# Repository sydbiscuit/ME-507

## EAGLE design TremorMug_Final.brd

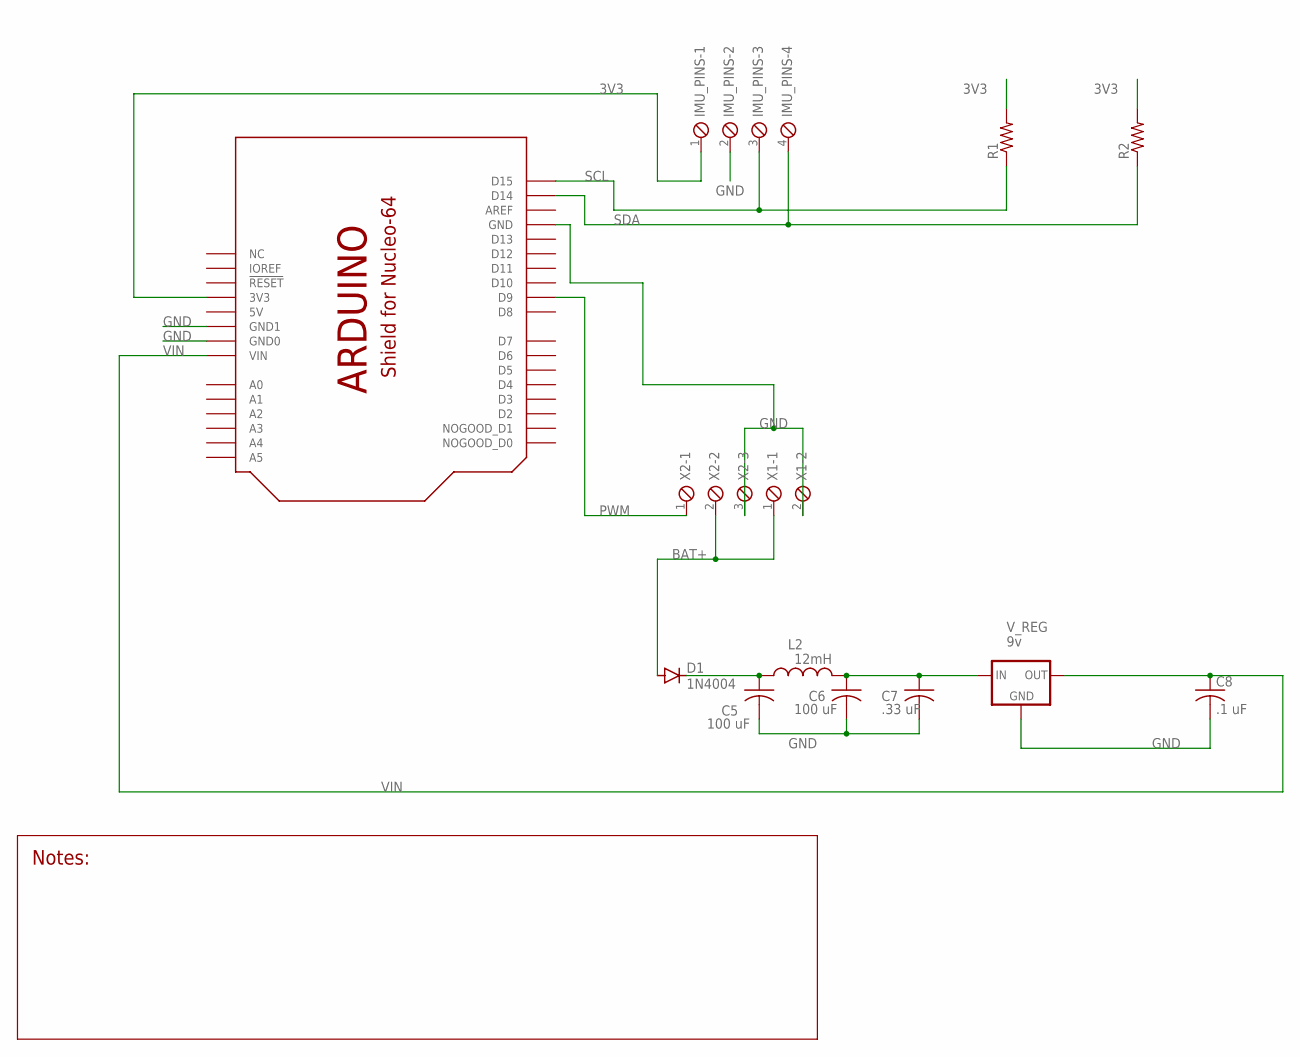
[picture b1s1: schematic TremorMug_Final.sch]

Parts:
C5, C6: 100 uF; C050-045X075
C7: .33 uF; C0805
C8: .1 uF; C0805
D1: 1N4004; DO41-10
IMU_PINS: SCREWTERM_4P_254; 4POL254
L2: 12mH; 0207/5V
R1, R2: R-US_0204/7; 0204/7
U$1: SHIELD_FOR_NUCLE0_64_STANDARD; SHIELD_FOR_NUCLEO_64_STD
V_REG: 9v; 78MXXL
X1: SCREWTERM_2P_508; 2POL508
X2: SCREWTERM_3P_381; 3POL381

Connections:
3V3: IMU_PINS.1, R1.2, R2.2, U$1.3V (3V3)
5V: U$1.5V
BAT+: D1.A, X1.1, X2.2
GND: C5.2, C6.2, C7.2, C8.2, IMU_PINS.2, U$1.GND, U$1.GND1 (GND0), U$1.GND2 (GND1), V_REG.GND, X1.2, X2.3
unnamed: C6.1, C7.1, L2.2, V_REG.IN
unnamed: C5.1, D1.C, L2.1
PWM: U$1.D9, X2.1
SCL: IMU_PINS.3, R1.1, U$1.D15
SDA: IMU_PINS.4, R2.1, U$1.D14
VIN: C8.1, U$1.VIN, V_REG.OUT

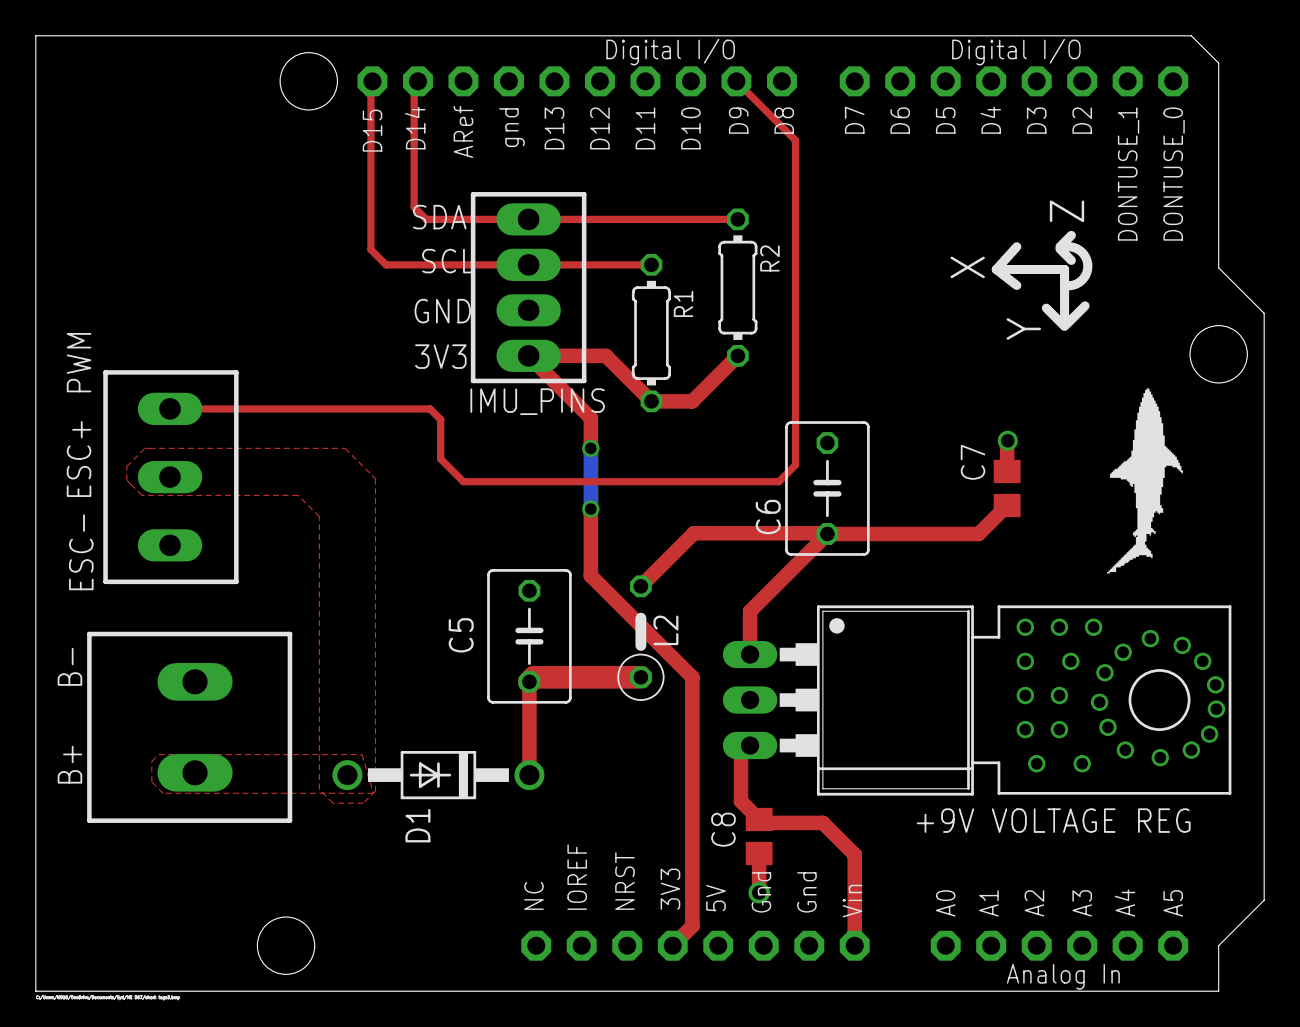
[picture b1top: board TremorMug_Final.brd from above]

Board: 2 copper layers, 68.6 x 53.3 mm, 13 parts (0 on the bottom side), 9 nets.

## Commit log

2021-11-29 updated comment test
2021-11-30 set frequency to 50hz
2021-11-30 clean up main file
2021-12-01 1ms pulse width comment
2021-12-01 First attempt at sending on/off signals without potentiometer
2021-12-01 Code powers motor for 5s then turns off for 10s
2021-12-07 Add files via upload
    Added documentation
2021-12-07 doxygen .html files for documentation
2021-12-07 Eagle PCB Files
2021-12-07 Controls 2 motors powering on for 0.5s and off for 1s
2021-12-08 Add files via upload
    Final Commit
